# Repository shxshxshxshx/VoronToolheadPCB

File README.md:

USB Toolhead Board for Voron Stealthburner

**WIP | DO NOT ORDER**

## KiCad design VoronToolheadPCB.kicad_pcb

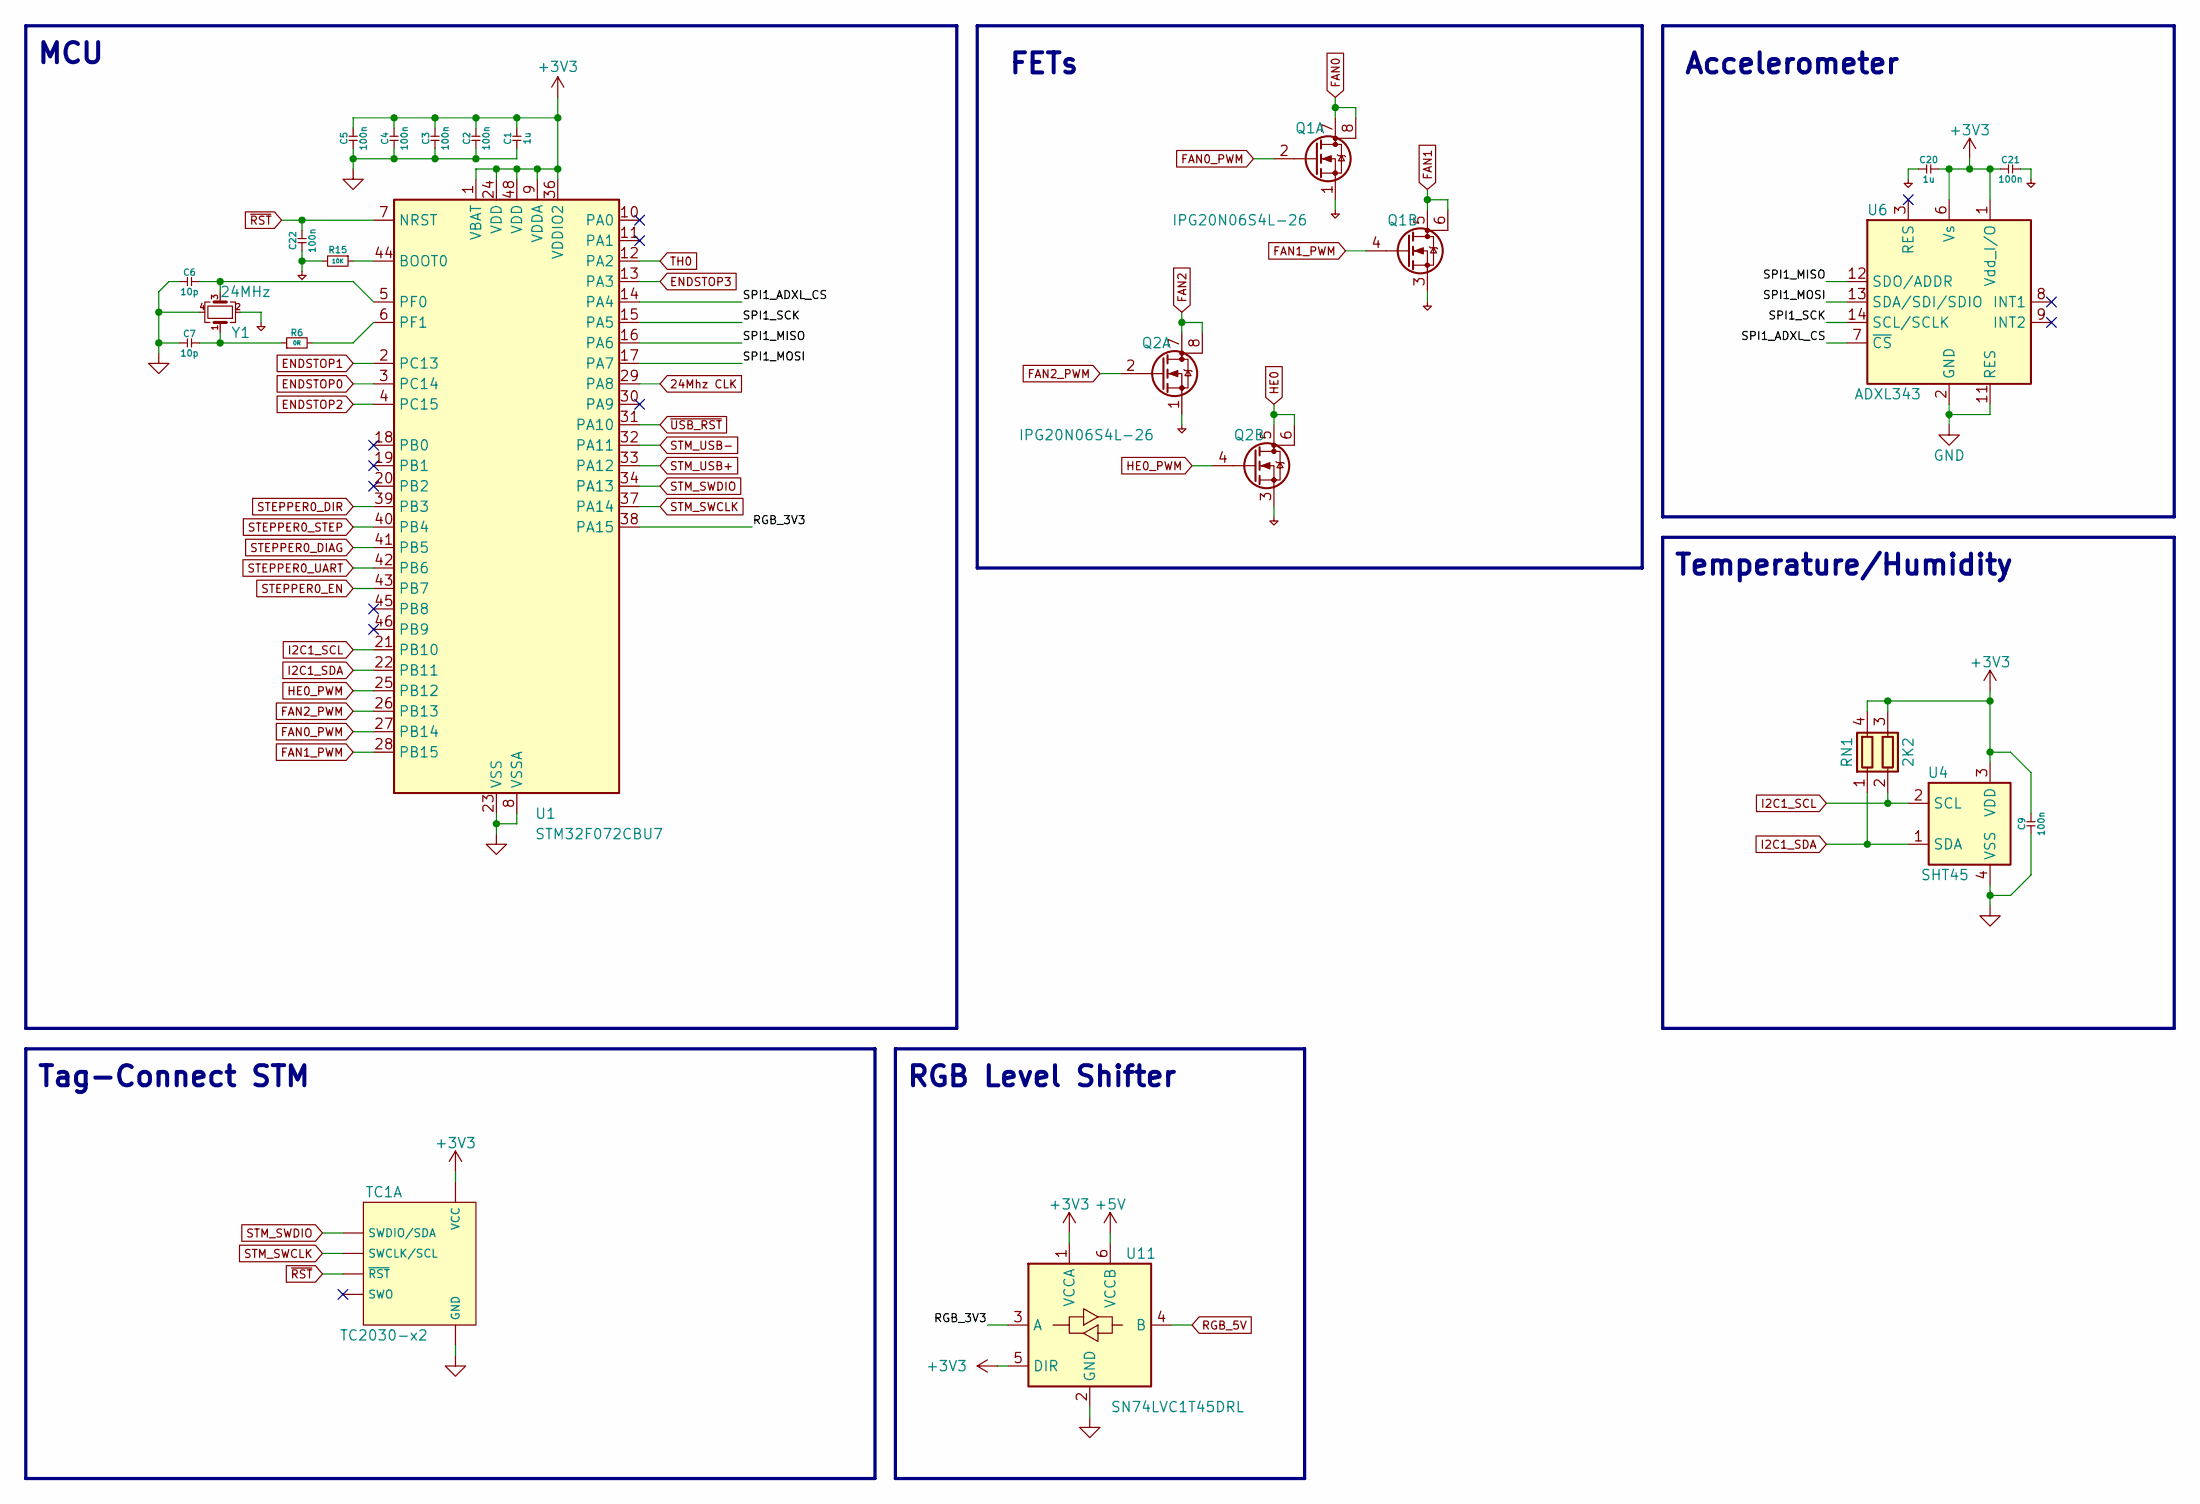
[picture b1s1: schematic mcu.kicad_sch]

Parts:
C1, C20: 1u; C_0402_1005Metric
C2, C3, C4, C5, C9, C21, C22: 100n; C_0402_1005Metric
C6, C7: 10p; C_0402_1005Metric
Q1, Q2: IPG20N06S4L-26; Infineon_PG-TDSON-8-4
R6: 0R; R_0402_1005Metric
R15: 10K; R_0402_1005Metric
RN1: 2K2; R_Array_Convex_2x0402
TC1: TC2030-x2; Double_Tag-Connect_TC2030-IDC-NL
U1: STM32F072CBU7; QFN-48-1EP_7x7mm_P0.5mm_EP5.6x5.6mm
U4: SHT45; Sensirion_DFN-4_1.5x1.5mm_P0.8mm_SHT4x_NoCentralPad
U6: ADXL343; LGA-14_3x5mm_P0.8mm_LayoutBorder1x6y
U11: SN74LVC1T45DRL; SOT-563
Y1: 24MHz; Crystal_SMD_2016-4Pin_2.0x1.6mm

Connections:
24Mhz CLK: U1.29 (PA8); also elsewhere on the board
+3V3: C1.2, C2.2, C3.2, C4.2, C5.2, C9.2, C20.2, C21.1, RN1.3 (R2.2), RN1.4 (R1.2), TC1.1 (VCC), U1.1 (VBAT), U1.9 (VDDA), U1.24 (VDD), U1.36 (VDDIO2), U1.48 (VDD), U4.3 (VDD), U6.1 (Vdd_I/O), U6.6 (Vs), U11.1 (VCCA), U11.5 (DIR); also elsewhere on the board
+5V: U11.6 (VCCB); also elsewhere on the board
/MCU/RGB_3V3: U1.38 (PA15), U11.3 (A)
/MCU/SPI1_ADXL_CS: U1.14 (PA4), U6.7 (~CS)
/MCU/SPI1_MISO: U1.16 (PA6), U6.12 (SDO/ADDR)
/MCU/SPI1_MOSI: U1.17 (PA7), U6.13 (SDA/SDI/SDIO)
/MCU/SPI1_SCK: U1.15 (PA5), U6.14 (SCL/SCLK)
ENDSTOP0: U1.3 (PC14); also elsewhere on the board
ENDSTOP1: U1.2 (PC13); also elsewhere on the board
ENDSTOP2: U1.4 (PC15); also elsewhere on the board
ENDSTOP3: U1.13 (PA3); also elsewhere on the board
FAN0: Q1.7 (D), Q1.8 (D); also elsewhere on the board
FAN0_PWM: Q1.2 (G), U1.27 (PB14)
FAN1: Q1.5 (D), Q1.6 (D); also elsewhere on the board
FAN1_PWM: Q1.4 (G), U1.28 (PB15)
FAN2: Q2.7 (D), Q2.8 (D); also elsewhere on the board
FAN2_PWM: Q2.2 (G), U1.26 (PB13)
GND: C1.1, C2.1, C3.1, C4.1, C5.1, C6.1, C7.1, C9.1, C20.1, C21.2, C22.1, Q1.1 (S), Q1.3 (S), Q2.1 (S), Q2.3 (S), R15.2, TC1.5 (GND), U1.8 (VSSA), U1.23 (VSS), U1.35 (VSS), U1.47 (VSS), U1.49 (VSS), U4.4 (VSS), U6.2 (GND), U6.4 (GND), U6.5 (GND), U6.11 (RES), U11.2 (GND), Y1.2, Y1.4; also elsewhere on the board
HE0: Q2.5 (D), Q2.6 (D); also elsewhere on the board
HE0_PWM: Q2.4 (G), U1.25 (PB12)
I2C1_SCL: RN1.2 (R2.1), U1.21 (PB10), U4.2 (SCL)
I2C1_SDA: RN1.1 (R1.1), U1.22 (PB11), U4.1 (SDA)
unnamed: C7.2, R6.1, Y1.1
unnamed: R15.1, U1.44 (BOOT0)
unnamed: C6.2, U1.5 (PF0), Y1.3
unnamed: R6.2, U1.6 (PF1)
RGB_5V: U11.4 (B); also elsewhere on the board
STEPPER0_DIAG: U1.41 (PB5); also elsewhere on the board
STEPPER0_DIR: U1.39 (PB3); also elsewhere on the board
STEPPER0_EN: U1.43 (PB7); also elsewhere on the board
STEPPER0_STEP: U1.40 (PB4); also elsewhere on the board
STEPPER0_UART: U1.42 (PB6); also elsewhere on the board
STM_SWCLK: TC1.4 (SWCLK/SCL), U1.37 (PA14)
STM_SWDIO: TC1.2 (SWDIO/SDA), U1.34 (PA13)
STM_USB+: U1.33 (PA12); also elsewhere on the board
STM_USB-: U1.32 (PA11); also elsewhere on the board
TH0: U1.12 (PA2); also elsewhere on the board
~RST: C22.2, TC1.3 (~RST), U1.7 (NRST)
~USB_RST: U1.31 (PA10); also elsewhere on the board

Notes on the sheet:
MCU
Tag-Connect STM
Accelerometer
Temperature/Humidity
FETs
RGB Level Shifter

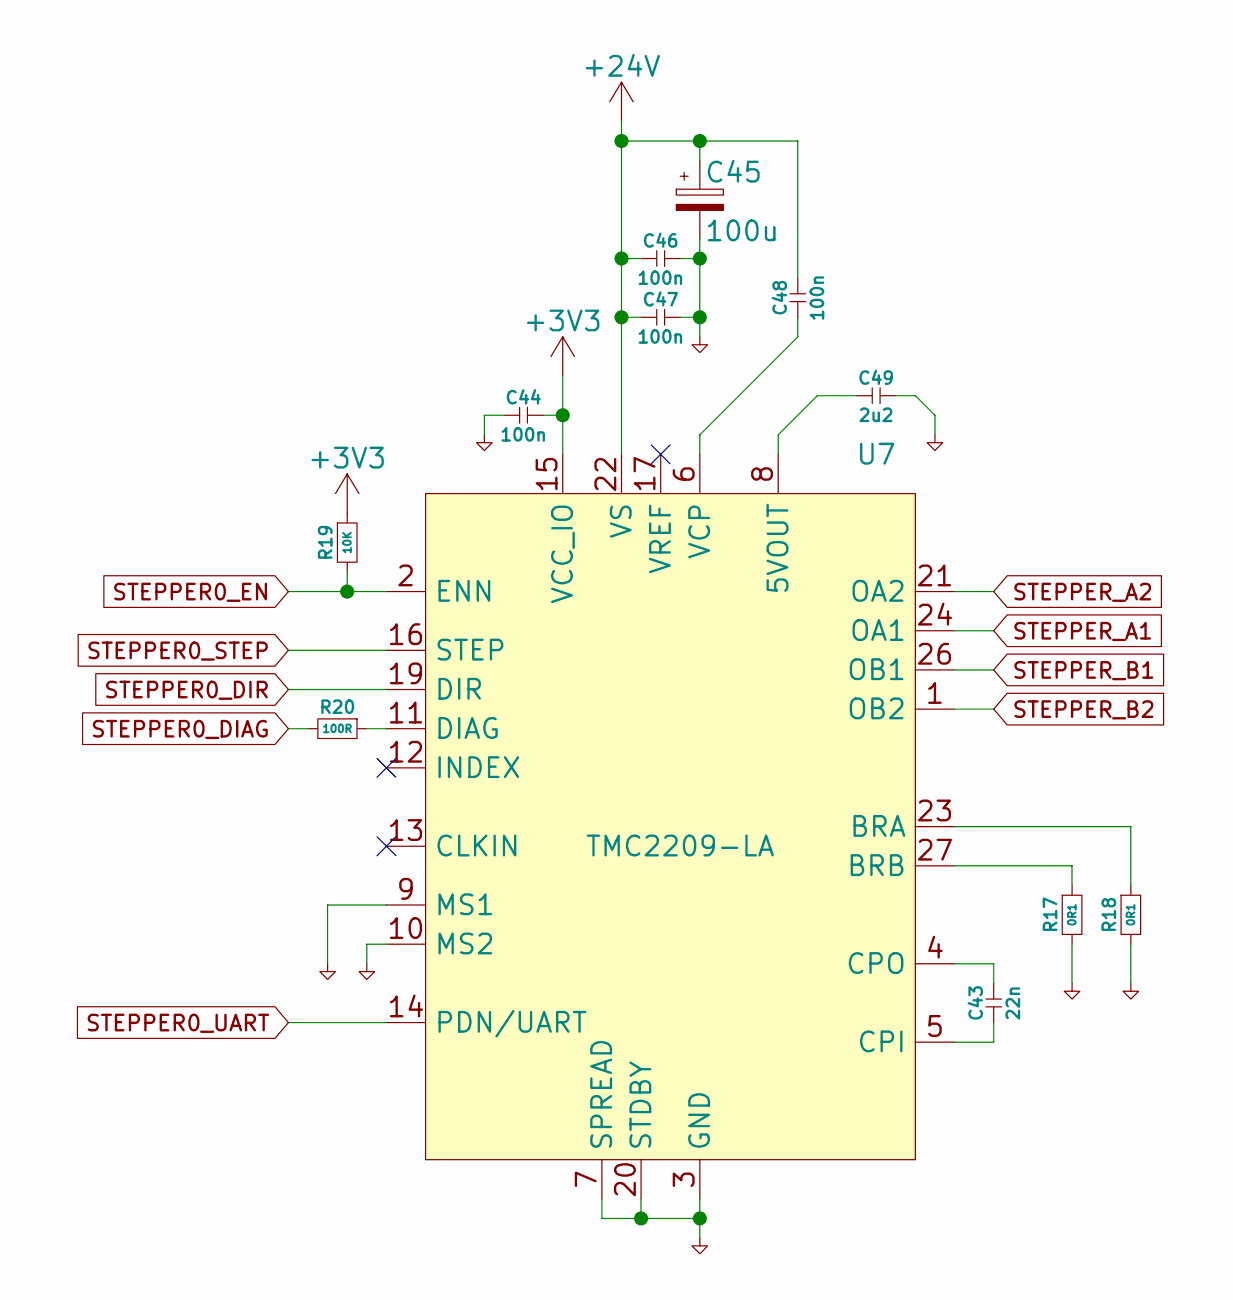
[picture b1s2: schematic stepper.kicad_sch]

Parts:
C43: 22n; C_0402_1005Metric
C44, C46, C47, C48: 100n; C_0402_1005Metric
C45: 100u; CP_Elec_6.3x7.7
C49: 2u2; C_0402_1005Metric
R17, R18: 0R1; R_0402_1005Metric
R19: 10K; R_0402_1005Metric
R20: 100R; R_0402_1005Metric
U7: TMC2209-LA; QFN-28-1EP_5x5mm_P0.5mm_EP3.75x3.75mm

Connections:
+3V3: C44.2, R19.1, U7.15 (VCC_IO); also elsewhere on the board
+24V: C45.1, C46.1, C47.1, C48.2, U7.22 (VS), U7.28 (VS); also elsewhere on the board
GND: C44.1, C45.2, C46.2, C47.2, C49.2, R17.2, R18.2, U7.3 (GND), U7.7 (SPREAD), U7.9 (MS1), U7.10 (MS2), U7.18 (GND), U7.20 (STDBY), U7.25, U7.29 (EP); also elsewhere on the board
unnamed: C49.1, U7.8 (5VOUT)
unnamed: R18.1, U7.23 (BRA)
unnamed: R17.1, U7.27 (BRB)
unnamed: C43.1, U7.5 (CPI)
unnamed: C43.2, U7.4 (CPO)
unnamed: R20.1, U7.11 (DIAG)
unnamed: C48.1, U7.6 (VCP)
STEPPER0_DIAG: R20.2; also elsewhere on the board
STEPPER0_DIR: U7.19 (DIR); also elsewhere on the board
STEPPER0_EN: R19.2, U7.2 (ENN); also elsewhere on the board
STEPPER0_STEP: U7.16 (STEP); also elsewhere on the board
STEPPER0_UART: U7.14 (PDN/UART); also elsewhere on the board
STEPPER_A1: U7.24 (OA1); also elsewhere on the board
STEPPER_A2: U7.21 (OA2); also elsewhere on the board
STEPPER_B1: U7.26 (OB1); also elsewhere on the board
STEPPER_B2: U7.1 (OB2); also elsewhere on the board

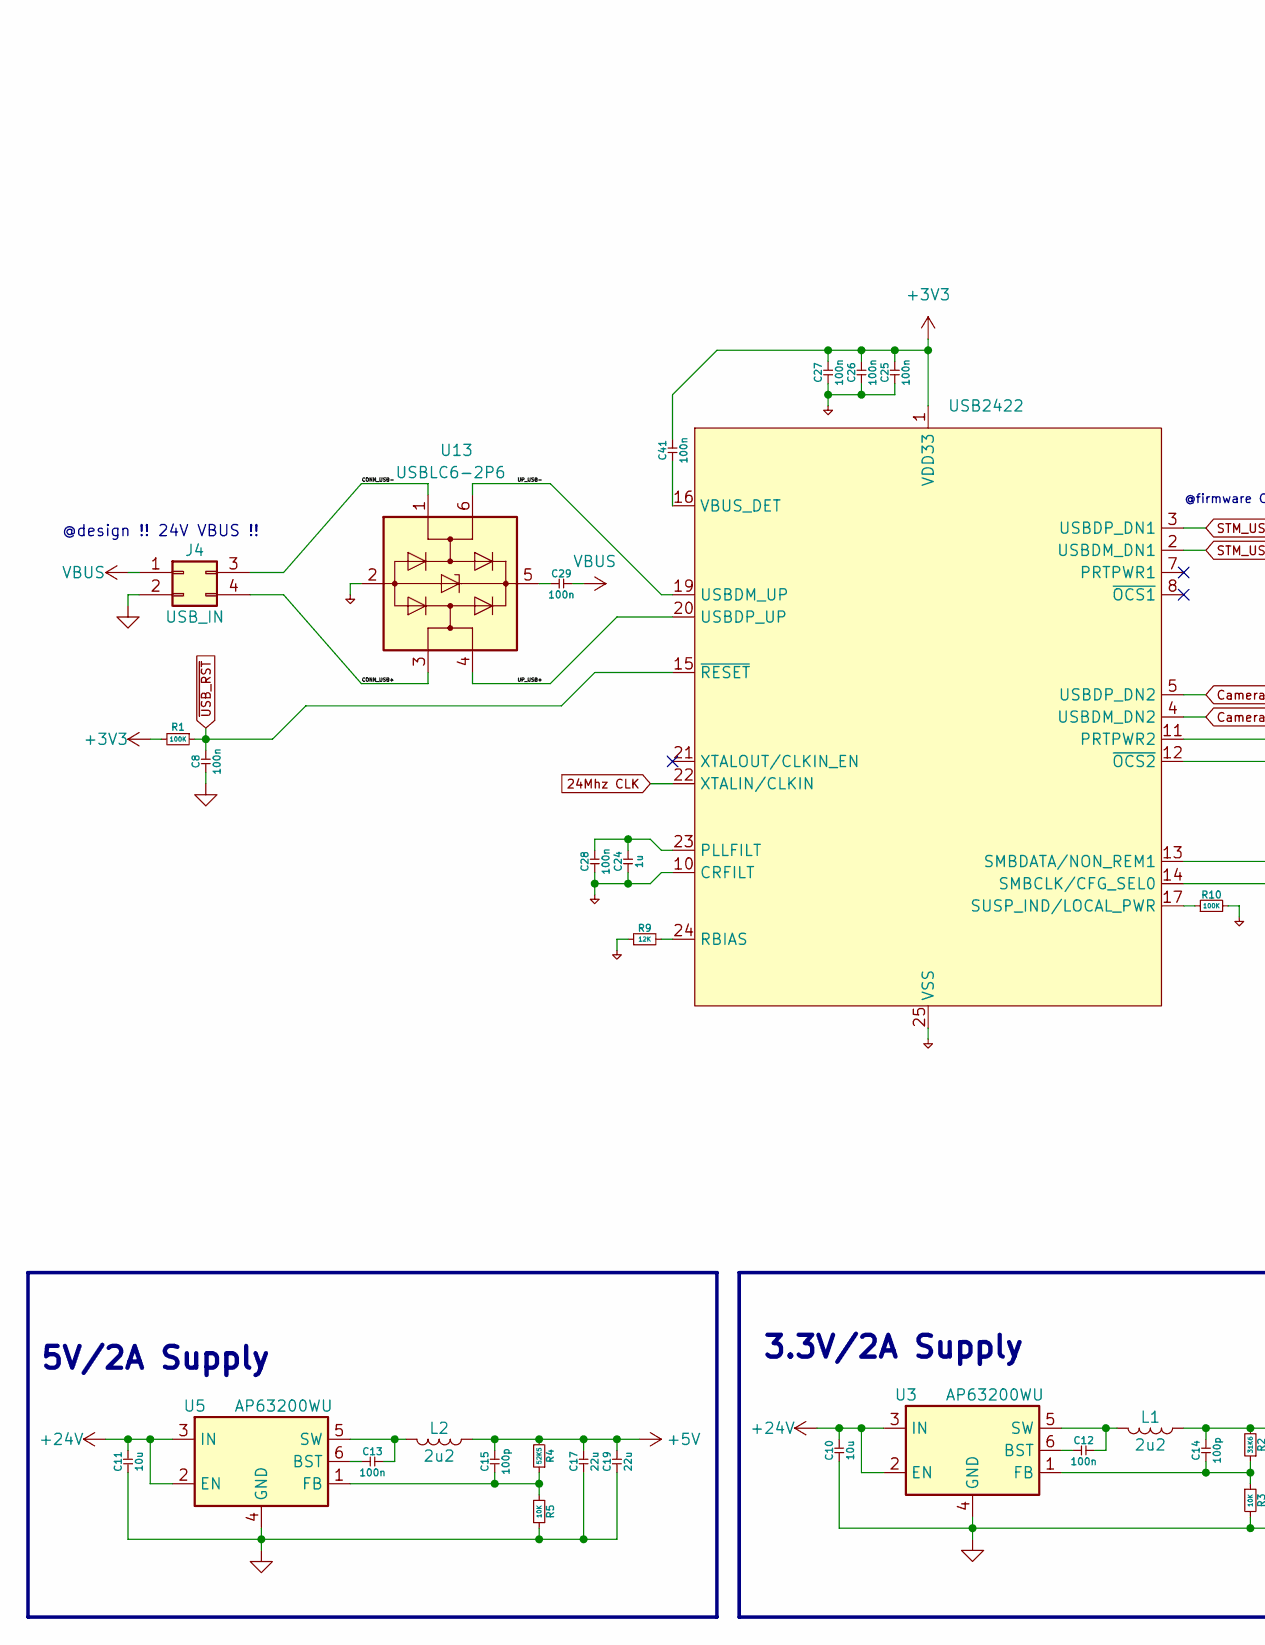
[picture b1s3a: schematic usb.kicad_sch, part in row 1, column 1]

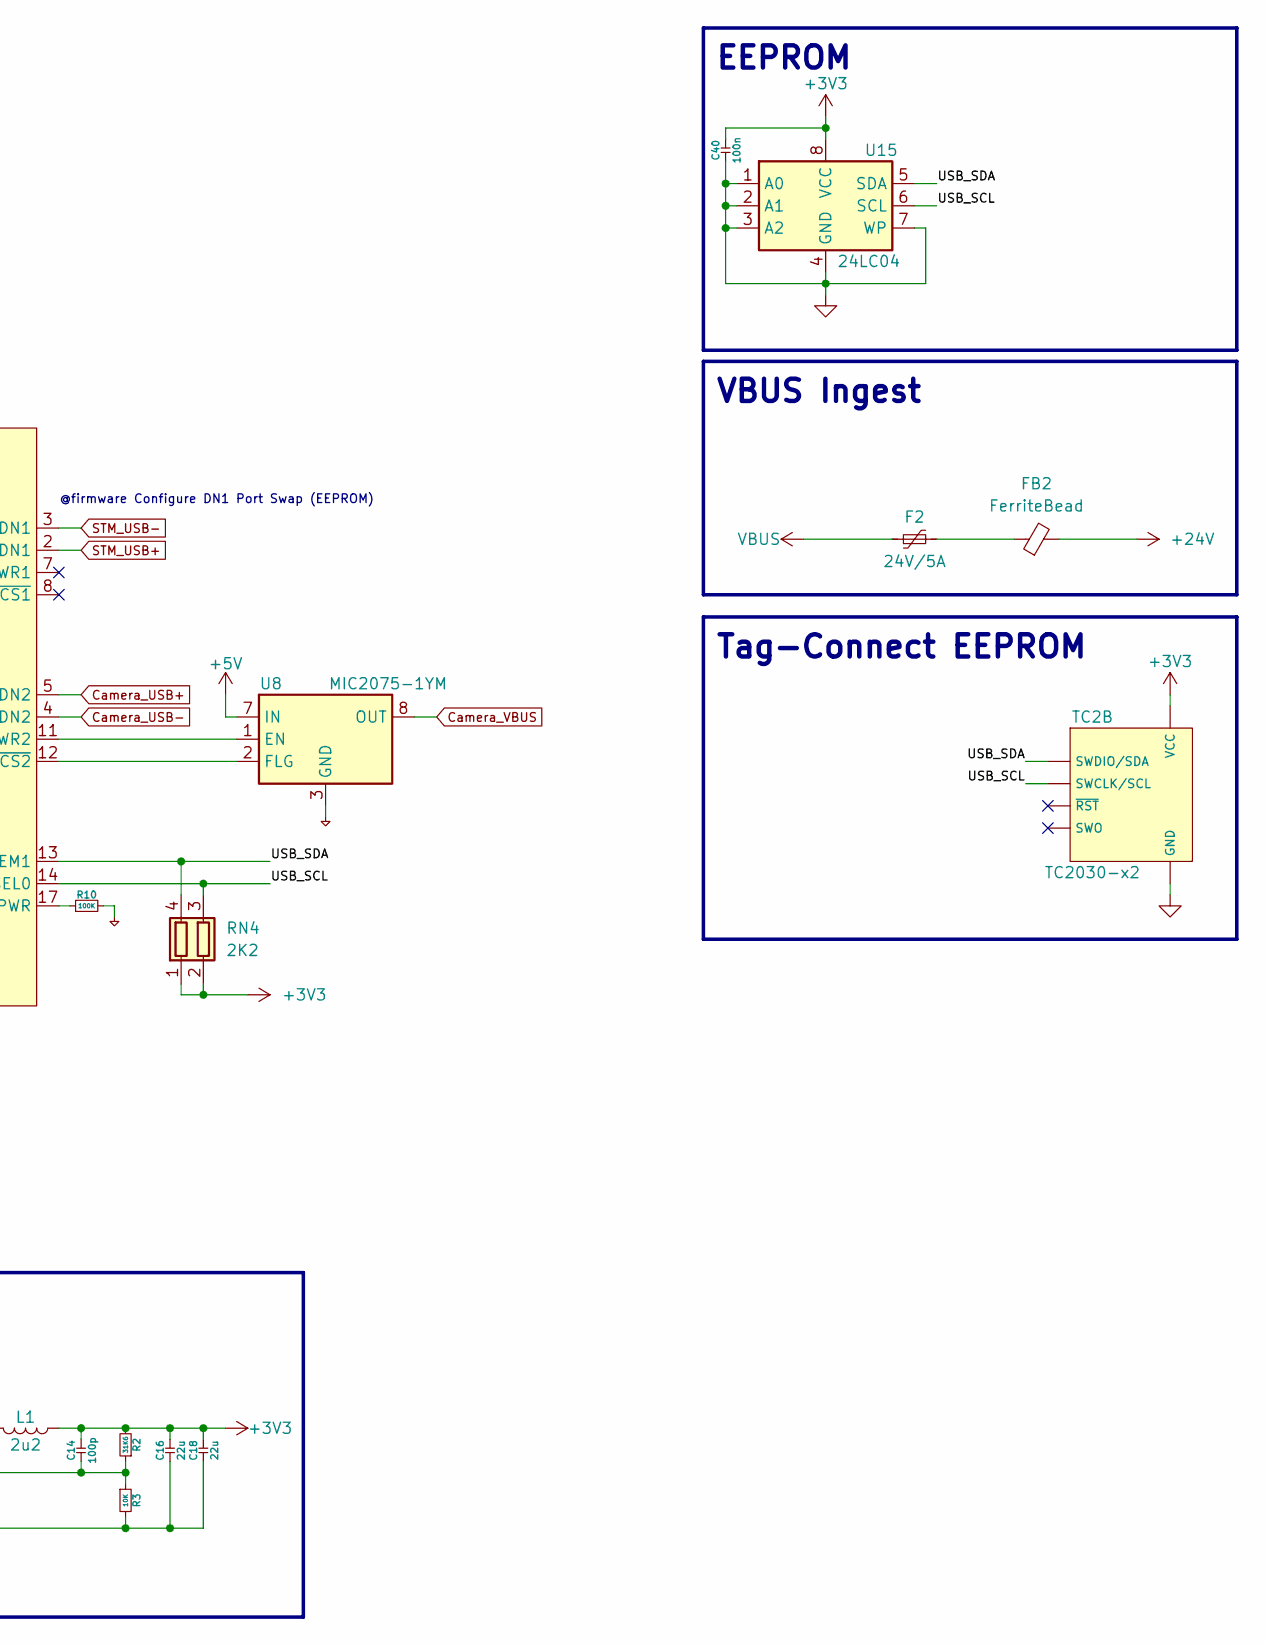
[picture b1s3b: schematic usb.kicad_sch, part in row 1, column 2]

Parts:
C8, C12, C13, C25, C26, C27, C28, C29, C40, C41: 100n; C_0402_1005Metric
C10, C11: 10u; C_0603_1608Metric
C14, C15: 100p; C_0402_1005Metric
C16, C17, C18, C19: 22u; C_0402_1005Metric
C24: 1u; C_0402_1005Metric
F2: 24V/5A; Fuse_0603_1608Metric
FB2: FerriteBead; L_0805_2012Metric
J4: USB_IN; Molex_Micro-Fit_3.0_43045-0400_2x02_P3.00mm_Horizontal
L1, L2: 2u2; L_1210_3225Metric
R1, R10: 100K; R_0402_1005Metric
R2: 31K6; R_0402_1005Metric
R3, R5: 10K; R_0402_1005Metric
R4: 52K5; R_0402_1005Metric
R9: 12K; R_0402_1005Metric
RN4: 2K2; R_Array_Convex_2x0402
TC2: TC2030-x2; Double_Tag-Connect_TC2030-IDC-NL
U2: USB2422; QFN-24-1EP_4x4mm_P0.5mm_EP2.6x2.6mm
U3, U5: AP63200WU; TSOT-23-6
U8: MIC2075-1YM; SOIC-8_3.9x4.9mm_P1.27mm
U13: USBLC6-2P6; SOT-666
U15: 24LC04; DFN-8-1EP_3x2mm_P0.5mm_EP1.36x1.46mm

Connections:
24Mhz CLK: U2.22 (XTALIN/CLKIN); also elsewhere on the board
+3V3: C14.2, C16.2, C18.2, C25.2, C26.2, C27.2, C40.2, C41.2, L1.1, R1.2, R2.2, RN4.1 (R1.1), RN4.2 (R2.1), U2.1 (VDD33), U2.9 (VDD33), U2.18 (VDD33), U15.8 (VCC); also elsewhere on the board
+5V: C15.2, C17.2, C19.2, L2.2, R4.2, U8.7 (IN); also elsewhere on the board
+24V: C10.2, C11.2, FB2.2, U3.2 (EN), U3.3 (IN), U5.2 (EN), U5.3 (IN); also elsewhere on the board
/USB/CONN_USB+: J4.4, U13.3 (I/O2)
/USB/CONN_USB-: J4.3, U13.1 (I/O1)
/USB/UP_USB+: U2.20 (USBDP_UP), U13.4 (I/O2)
/USB/UP_USB-: U2.19 (USBDM_UP), U13.6 (I/O1)
/USB/USB_SCL: RN4.3 (R2.2), U2.14 (SMBCLK/CFG_SEL0), U15.6 (SCL); also elsewhere on the board
/USB/USB_SDA: RN4.4 (R1.2), U2.13 (SMBDATA/NON_REM1), U15.5 (SDA); also elsewhere on the board
Camera_USB+: U2.5 (USBDP_DN2); also elsewhere on the board
Camera_USB-: U2.4 (USBDM_DN2); also elsewhere on the board
Camera_VBUS: U8.6 (OUT), U8.8 (OUT); also elsewhere on the board
GND: C8.1, C10.1, C11.1, C16.1, C17.1, C18.1, C19.1, C24.1, C25.1, C26.1, C27.1, C28.1, C40.1, J4.2, R3.2, R5.2, R9.1, R10.2, U2.10 (CRFILT), U2.25 (VSS), U3.4 (GND), U5.4 (GND), U8.3 (GND), U13.2 (GND), U15.1 (A0), U15.2 (A1), U15.3 (A2), U15.4 (GND), U15.7 (WP), U15.9; also elsewhere on the board
unnamed: F2.2, FB2.1
unnamed: C24.2, C28.2, U2.23 (PLLFILT)
unnamed: U2.11 (PRTPWR2), U8.1 (EN)
unnamed: R9.2, U2.24 (RBIAS)
unnamed: R10.1, U2.17 (SUSP_IND/LOCAL_PWR)
unnamed: C41.1, U2.16 (VBUS_DET)
unnamed: U2.12 (~OCS2), U8.2 (FLG)
unnamed: C12.1, U3.6 (BST)
unnamed: C14.1, R2.1, R3.1, U3.1 (FB)
unnamed: C12.2, L1.2, U3.5 (SW)
unnamed: C13.1, U5.6 (BST)
unnamed: C15.1, R4.1, R5.1, U5.1 (FB)
unnamed: C13.2, L2.1, U5.5 (SW)
unnamed: C29.1, U13.5 (VBUS)
STM_USB+: U2.2 (USBDM_DN1); also elsewhere on the board
STM_USB-: U2.3 (USBDP_DN1); also elsewhere on the board
VBUS: C29.2, F2.1, J4.1
~USB_RST: C8.2, R1.1, U2.15 (~RESET); also elsewhere on the board

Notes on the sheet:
@design !! 24V VBUS !!
VBUS Ingest
3.3V/2A Supply
5V/2A Supply
EEPROM
Tag-Connect EEPROM
@firmware Configure DN1 Port Swap (EEPROM)

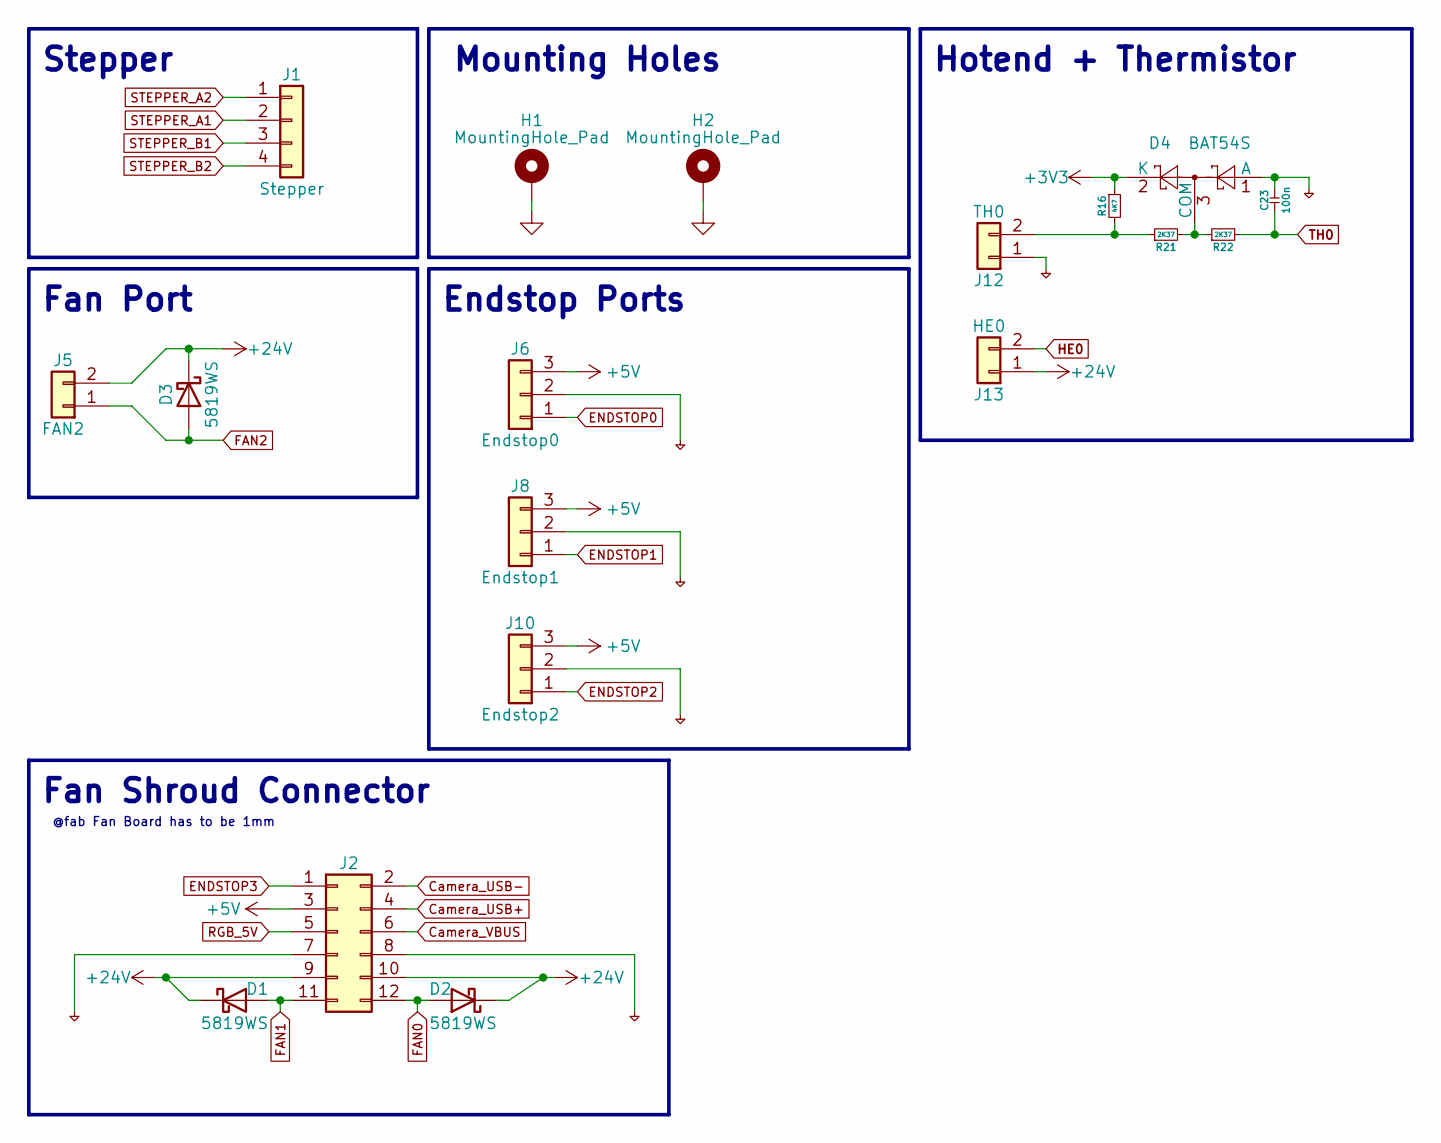
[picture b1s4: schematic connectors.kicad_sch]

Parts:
C23: 100n; C_0402_1005Metric
D1, D2, D3: 5819WS; D_SOD-323
D4: BAT54S; SOT-23
H1, H2: MountingHole_Pad; MountingHole_3.2mm_M3_DIN965_Pad
J1: Stepper; JST_PH_B4B-PH-SM4-TB_1x04-1MP_P2.00mm_Vertical
J2: Conn_02x06_Odd_Even; PinSocket_2x06_P2.00mm_Horizontal
J5: FAN2; JST_PH_B2B-PH-K_1x02_P2.00mm_Vertical
J6: Endstop0; JST_PH_B3B-PH-K_1x03_P2.00mm_Vertical
J8: Endstop1; JST_PH_B3B-PH-K_1x03_P2.00mm_Vertical
J10: Endstop2; JST_PH_B3B-PH-K_1x03_P2.00mm_Vertical
J12: TH0; JST_PH_S2B-PH-SM4-TB_1x02-1MP_P2.00mm_Horizontal
J13: HE0; Molex_Micro-Fit_3.0_43650-0200_1x02_P3.00mm_Horizontal
R16: 4K7; R_0402_1005Metric
R21, R22: 2K37; R_0402_1005Metric

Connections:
+3V3: D4.2 (K), R16.1; also elsewhere on the board
+5V: J2.3, J6.3, J8.3, J10.3; also elsewhere on the board
+24V: D1.1 (K), D2.1 (K), D3.1 (K), J2.9, J2.10, J5.2, J13.1; also elsewhere on the board
Camera_USB+: J2.4; also elsewhere on the board
Camera_USB-: J2.2; also elsewhere on the board
Camera_VBUS: J2.6; also elsewhere on the board
ENDSTOP0: J6.1; also elsewhere on the board
ENDSTOP1: J8.1; also elsewhere on the board
ENDSTOP2: J10.1; also elsewhere on the board
ENDSTOP3: J2.1; also elsewhere on the board
FAN0: D2.2 (A), J2.12; also elsewhere on the board
FAN1: D1.2 (A), J2.11; also elsewhere on the board
FAN2: D3.2 (A), J5.1; also elsewhere on the board
GND: C23.2, D4.1 (A), H1.1, H2.1, J1.MP, J2.7, J2.8, J6.2, J8.2, J10.2, J12.1; also elsewhere on the board
HE0: J13.2; also elsewhere on the board
unnamed: D4.3 (COM), R21.2, R22.1
unnamed: J12.2, R16.2, R21.1
RGB_5V: J2.5; also elsewhere on the board
STEPPER_A1: J1.2; also elsewhere on the board
STEPPER_A2: J1.1; also elsewhere on the board
STEPPER_B1: J1.3; also elsewhere on the board
STEPPER_B2: J1.4; also elsewhere on the board
TH0: C23.1, R22.2; also elsewhere on the board

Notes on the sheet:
Fan Shroud Connector
Fan Port
Hotend + Thermistor
@fab Fan Board has to be 1mm
Endstop Ports
Mounting Holes
Stepper

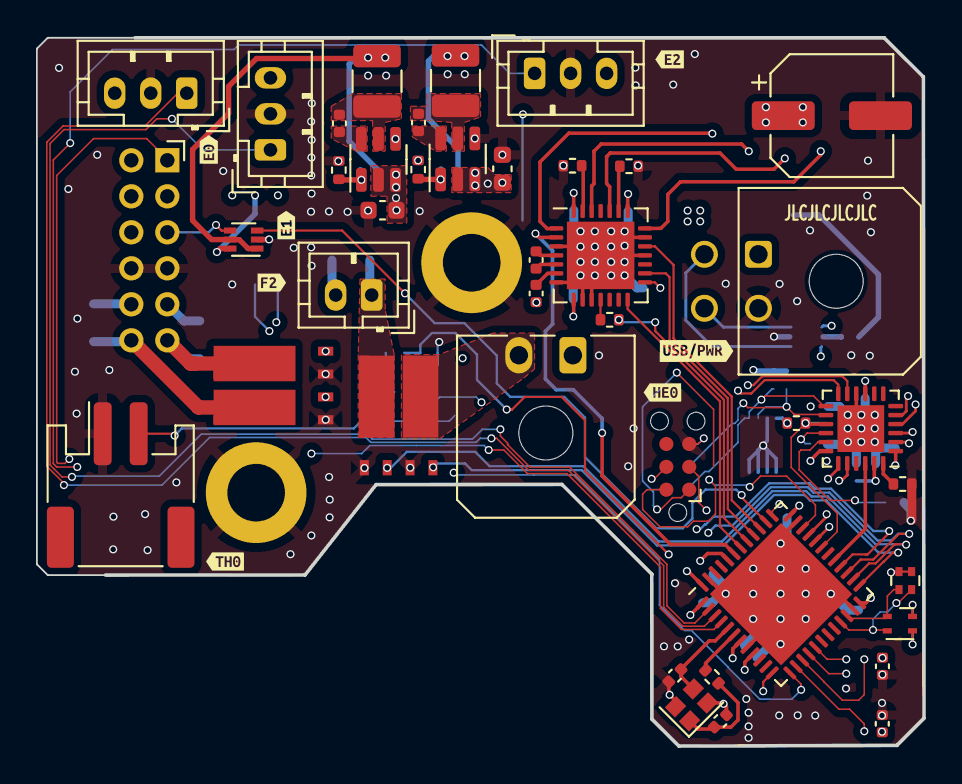
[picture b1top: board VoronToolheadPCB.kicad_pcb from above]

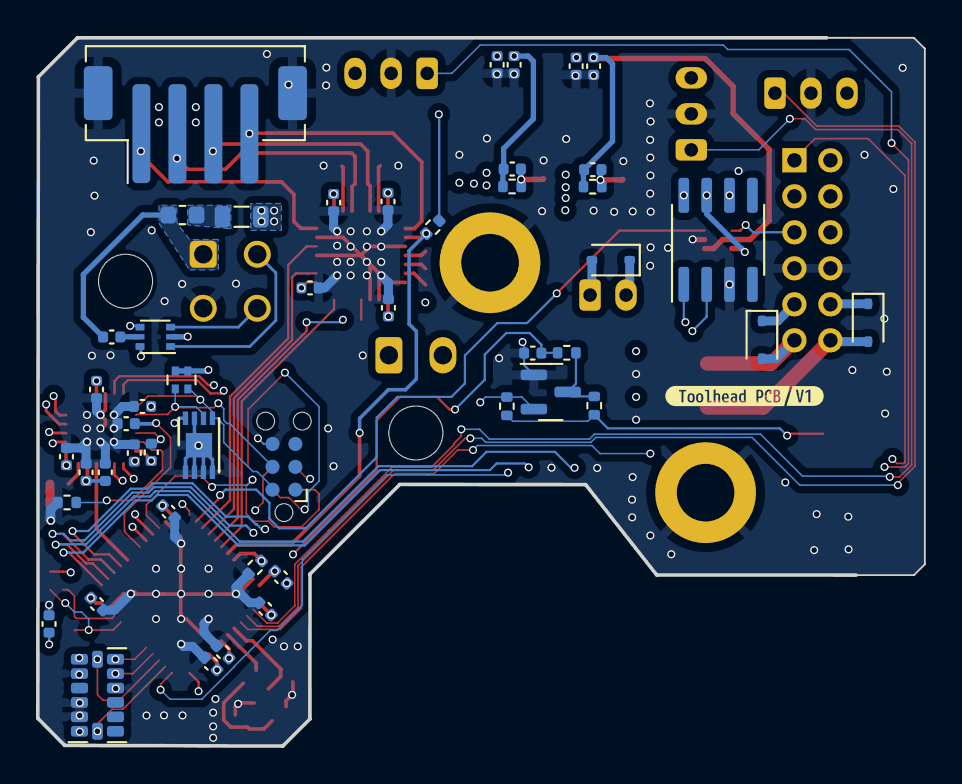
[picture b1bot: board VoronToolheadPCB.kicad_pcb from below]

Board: 6 copper layers, 49.2 x 39.3 mm, 99 parts (49 on the bottom side), 78 nets.

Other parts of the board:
kibuzzard-651F31B1: G***; kibuzzard-651F31B1
kibuzzard-651F31F1: G***; kibuzzard-651F31F1
kibuzzard-651F32E5: G***; kibuzzard-651F32E5
kibuzzard-651F32EB: G***; kibuzzard-651F32EB
kibuzzard-651F311C: G***; kibuzzard-651F311C
kibuzzard-651F318A: G***; kibuzzard-651F318A
kibuzzard-651F3142: G***; kibuzzard-651F3142
kibuzzard-651F3160: G***; kibuzzard-651F3160
kibuzzard-651F3191: G***; kibuzzard-651F3191

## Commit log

2023-10-27 Initial
2023-10-27 added pictures to Readme
